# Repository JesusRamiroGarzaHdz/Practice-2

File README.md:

# Practice 2. Developiong the PCB (Layout)

## Objectives

Develop the connection diagrams (layout) from the schematic diagram.

## Introduction

Microcontrollers are all around  he world. Each day, Microcontrollers, are more present in the many aspects of our lives: in our work, inside our houses, and in more. We can find them controlling small devices like cellphones, microwaves, washing machines, and televisions.

A microcontroller is one device or chip that is used to govern one or more processes. For example, the controller that regulates the room temperature of an air conditioner; it has a sensor that continuously measures the internal temperature and, when the preset limits are exceeded, it generates the necessary signals to adjust the temperature.

## State of the Art

### The practices and the PIC microcontroller

The main objective of this practices is to provide students the foundation to fully understand the operation of the PIC18F45K50 microcontroller. This will be achieved through 11 documents that will guide the reader to create their own electronic card or Printed Circuit Board (PCB) and to be able to program it; in order to, execute different functions.

The advantages of ta PIC microcontroller to others on the market, which is why it will be used throughout this manual, are as follows:

- Easy to operate.
- There is enough documentation to work with it and it’s easy to obtain it.
- The price is comparatively lower than its competitors.
- It has a high operating speed.
- Development tools are cheap and easy to use.
- There are a variety of hardware that can record, erase and check the behavior of PIC.
- Once you learn to handle a PIC, it will easier to handle any other models of microcontrollers.

### KiCad EDA Software

KiCad is an open source software suite for Electronic Design Automation (EDA). The programs handle Schematic Capture,
and PCB Layout with Gerber output. The suite runs on Windows, Linux and macOS and is licensed under GNU GPL v3. The
first release date was in 1992 by its original author, Jean-Pierre Charras, but is now currently under development by
the KiCad Developers Team. 

## Results

In this section, you must report the outcomes of the laboratory activities.

### Follow the next 'Project Configuration' Steps

1. In  the  same  project  from  practice  1,  click  on  the  icon ‘Assign PCB footprints to schematic symbols’.  By  doing  so,  you  will  be  able  to  watch  the  footprints associations in a list format. ***NOTE:*** *If a ***‘Confirmation’*** window pops to reassign all the components to a new library format, click ‘No.’*

2. Now it is time to add the corresponding libraries to the Cvpcbprogram.   Download from [here](./modules)  the modules   needed   for   the   project.   Click   on Preferences→Manage Footprint Libraries...and  in this  way  you  will  be  able  to  add  the  modules  from the folder  named  ‘modules.’  Click  on  ‘Project  Specific Libraries...’  tab,  then  click  on  the  button  ‘Browse Libraries...’ and search for the folder  where  you  save the modules. Select all the files and click ‘OK.’Fig.  1 shows the result of the added modules. NOTE:Your KiCad EDA Software must be in english to add the modules.

3. Once  that  is  done,  you  must  associate  the  list  of components  with  its  respective  footprint using Table  I for  guidance.  Be  sure  to  activate  the  option  ‘Filter footprints  list  by  library’ from  the Cvpcbtoolbar. To associate  the  components  showed  in  the middle  column,  double  click  with  their  corresponding footprint from the right column. ***NOTE:*** *Search  all  the  footprints  in  the*  ***‘user’*** *and * 
***‘discrete’*** * added libraries that should be found at the end of the list.*

4. Save   your modifications  by  clicking  **‘Apply,  Save Schematic & Continue,’ and then click ‘OK.’**
5. After that, you may close the Cvpcband go back to the EESchema (Schematic  Editor.)  Save  your  project  by clicking   on File→Save.   Close   the   editor   of   the Schematic and switch back to the **‘Project Manager.’**

6. Once you have the design of the circuit on the schematic, it is time to generate the **‘layout’** of our PCB  using the Netlist  file. On  the Project  Manager program  from KiCad, click on the icon **‘PCB layout editor’** . A new window will appear from the PCBNew. Click **‘Yes’** in the confirmation window.
7. On  the  toolbar  menu  from  the PCBNew click  on  the **‘Page  Settings  for  paper  size  and  texts’**
and modify the size settings to **‘USLetter 8.5x11in.’**

8. After  that,  it  will be  time  to  focus  more  on  design concepts.  You  may  do  so  by  opening  the
menu  of **‘Setup→Design Rules...’**. On   it,   some   final   design characteristics will appear with many millimeter values. Between   them,   you   should   find  the  **‘Clearance’** specification  which  is  the  smallest  spaces  that  it  must exist  between  the tracks  on the  PCB.  You  shall  set the value of this cell to 0.508 mm (0.020 inches.) Next, we set  a  value  of 1.200  mm  (0.047244 inches)on the  cell of **‘Track Width.’** 

9. Switch now to the ‘Global Design Rules’ tab and write, if needed, the minimum values for each an every one of the parameters on the ‘Minimum Allowed Values’ box. Click ‘OK.’

10. Time  to  import  the  Netlist  file.  Go  to  the  toolbar ‘Tools→Update  PCB  from  Schematic...’  and  then click on ‘Update  PCB.’ When  you  close  the  window all the components will appear on the screen.

11.Check in the ‘Layers Manager’ window (located at the right  part  of  your  screen) that all  the needed  boxes  are
checked, as shown:

11.Check in the ‘Layers Manager’ window (located at the right  part  of  your  screen) that all  the needed  boxes  are checke

12. Now you  have  to  define  the  limits  of  the  PCB.  First, highlight  the  ‘Edge.Cuts’  layer.  Then,  select  the  ‘Add  graphic lines’ tool and began to trace the original measures of your copper board (15x20 cm.) You must also define the  cutting  area;  do  not  forget  to  add  a  2.5  cm  margin around the board. To measure the lines, you can use the ‘Add dimension’ tool located on the right.

13. It is your turn to move all the components in the circuit in  order  to  avoid  any  track  intersection  inside  the working   area.   You   can   move   the   components   by positioning your mouse pointer above it and pressing the key [G]. All the components are connected to each other by a group of wires called ratsnest. Make sure that the icon  of  **‘Hide  board  ratsnest’** located  in  the toolbar of the left is highlighted.

14. Now you must link all the connections of you PCB. But before  that,  you  must  change  the  drawing  option  from the right toolbar from ‘Edge.Cuts’ to ‘B.Cu (PgDn)’ (B->Bottom, Cu->Copper.).

15. Start to connect your tracks to each and every one pin on the schematic by using the icon ‘Route Tracks’. Trace  all  the  routes  for  each  net  or  connection  in  your PCB design.

16. Once  your  are  done,  save  your  layout  File->Save  or using the command [Ctrl + S].

17. Your board must look like:

### Report
For this practice, modify only the Conclusion section. Commit an push the changes on the fork of this repository and add
upload the link on Canvas.

### File uploads
Commit and push the files with extensions .pro and .kicad_pcb created once you completed all the steps of the document in the repository.

### Demonstration
Screenshot the image of the complete schematic and upload it at the repository.

## Conclusion

In this second practice we learned how to develop a PCB (layer) for our proyect, this laboratory was by far the hardest one to complete because of the complexity of the software and our lack of experience in this topics. Personally, I had a problem with the libaries that we where asked to use por this practice, in 2 different points during the proccess, the program detected an error in my libraries and marked all my components as "unkonwn" erasing them form my schematic so I had to restart the practice. It was difficult and I had to ask for help to other classmates but at the end I managed to complete the practice and I think I solved it correctly. It was defenitely a bigger challenge than practice 1 but I consider that I have learned a lot about Kicad and how to use it to develop PCBs.

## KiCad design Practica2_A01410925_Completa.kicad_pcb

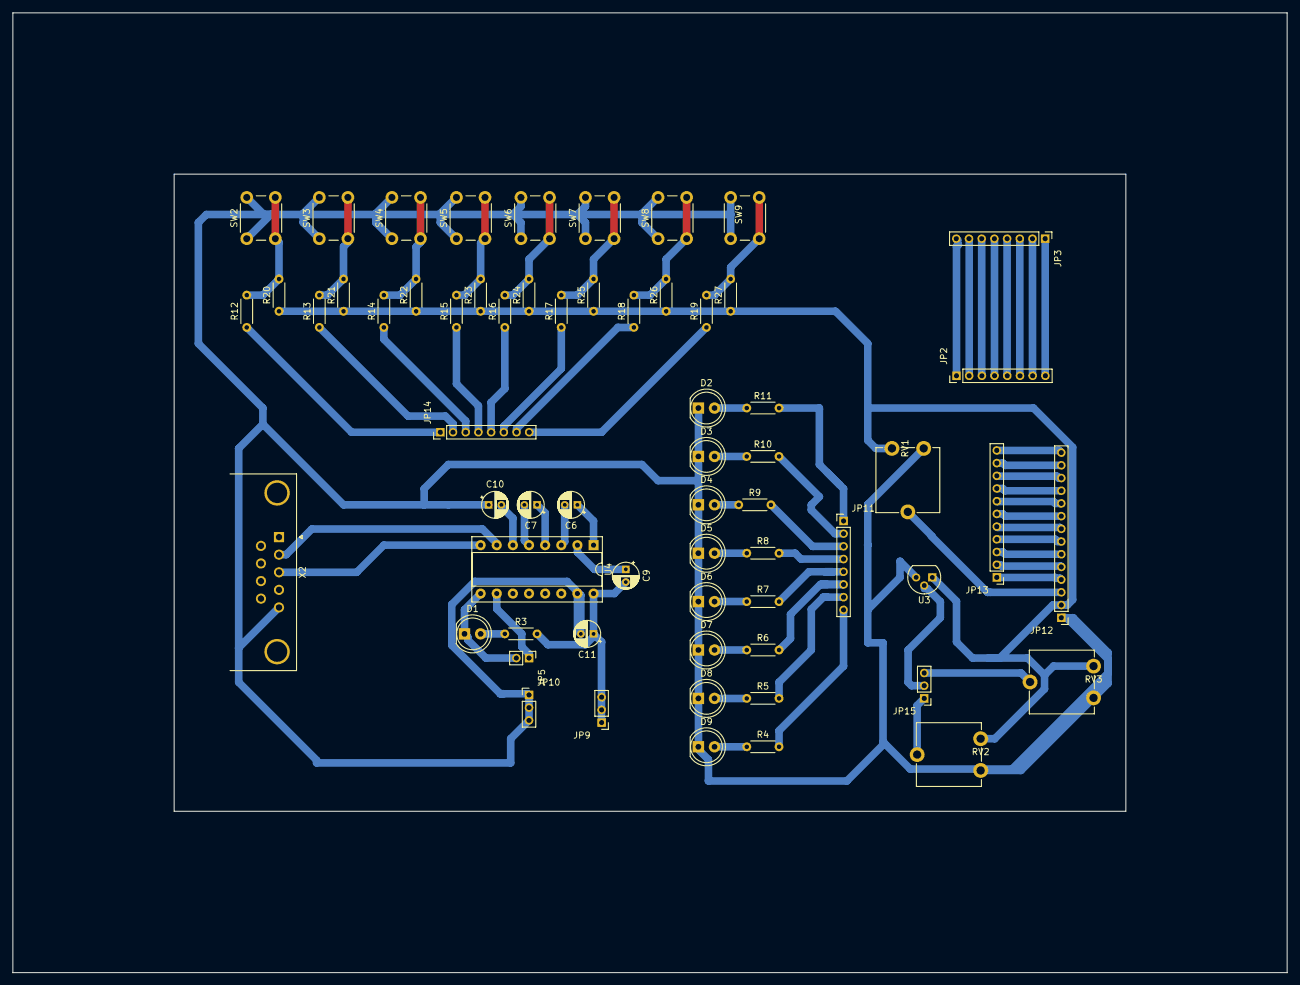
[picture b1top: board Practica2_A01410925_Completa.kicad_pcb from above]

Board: 2 copper layers, 200.7 x 151.1 mm, 63 parts (0 on the bottom side), 68 nets.

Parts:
C6, C7, C9, C10, C11: 10U; CP_Radial_D4.0mm_P2.00mm
D1, D2, D3, D4, D5, D6, D7, D8, D9: LED; LED_D5.0mm
JP2, JP3, JP11, JP14: PINHD-1X8; PinHeader_1x08_P2.00mm_Vertical
JP5: PINHD-1X2; PinHeader_1x02_P2.00mm_Vertical
JP9, JP10, JP15: PINHD-1X3; PinHeader_1x03_P2.00mm_Vertical
JP12: PINHD-1X14; PinHeader_1x14_P2.00mm_Vertical
JP13: PINHD-1X11; PinHeader_1x11_P2.00mm_Vertical
R3, R4, R5, R6, R7, R8, R9, R10, R11: 470; R_Axial_DIN0204_L3.6mm_D1.6mm_P5.08mm_Horizontal
R12, R13, R14, R15, R16, R17, R18, R19: 1K; R_Axial_DIN0204_L3.6mm_D1.6mm_P5.08mm_Horizontal
R20, R21, R22, R23, R24, R25, R26, R27: 4.7K; R_Axial_DIN0204_L3.6mm_D1.6mm_P5.08mm_Horizontal
RV1, RV2, RV3: 10K; Potentiometer_ACP_CA9-V10_Vertical
SW2, SW3, SW4, SW5, SW6, SW7, SW8, SW9: SW_Push; SW_PUSH_6mm
U3: MCP9700A; TO-92
U4: MAX232; DIP-16_W7.62mm_Socket
X2: F09HP; DSUB-9_Male_Horizontal_P2.77x2.84mm_EdgePinOffset4.94mm_Hou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

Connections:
+5VA: C9.2, C11.1, JP9.1, JP9.2, JP9.3, JP12.2, R3.2, R20.1, R21.1, R22.1, R23.1, R24.1, R25.1, R26.1, R27.1, RV1.1, RV2.1, RV3.1, U3.1, U4.16
GNDA: C10.1, C11.2, D2.1, D3.1, D4.1, D5.1, D6.1, D7.1, D8.1, D9.1, JP10.1, JP10.2, JP10.3, JP12.1, RV1.3, RV2.3, RV3.3, SW2.1, SW3.1, SW4.1, SW5.1, SW6.1, SW7.1, SW8.1, SW9.1, U3.3, U4.15, X2.5
unnamed: C6.1, U4.1
unnamed: C6.2, U4.3
unnamed: C7.1, U4.4
unnamed: C7.2, U4.5
unnamed: C9.1, U4.2
unnamed: C10.2, U4.6
unnamed: D1.1, JP5.2, U4.9
unnamed: D1.2, R3.1
unnamed: D2.2, R11.1
unnamed: D3.2, R10.1
unnamed: D4.2, R9.1
unnamed: D5.2, R8.1
unnamed: D6.2, R7.1
unnamed: D7.2, R6.1
unnamed: D8.2, R5.1
unnamed: D9.2, R4.1
unnamed: JP2.1, JP3.8
unnamed: JP2.2, JP3.7
unnamed: JP2.3, JP3.6
unnamed: JP2.4, JP3.5
unnamed: JP2.5, JP3.4
unnamed: JP2.6, JP3.3
unnamed: JP2.7, JP3.2
unnamed: JP2.8, JP3.1
unnamed: JP5.1, U4.10
unnamed: JP11.1, R11.2
unnamed: JP11.2, R10.2
unnamed: JP11.3, R9.2
unnamed: JP11.4, R8.2
unnamed: JP11.5, R7.2
unnamed: JP11.6, R6.2
unnamed: JP11.7, R5.2
unnamed: JP11.8, R4.2
unnamed: JP12.3, RV1.2
unnamed: JP12.4, JP13.1
unnamed: JP12.5, JP13.2
unnamed: JP12.6, JP13.3
unnamed: JP12.7, JP13.4
unnamed: JP12.8, JP13.5
unnamed: JP12.9, JP13.6
unnamed: JP12.10, JP13.7
unnamed: JP12.11, JP13.8
unnamed: JP12.12, JP13.9
unnamed: JP12.13, JP13.10
unnamed: JP12.14, JP13.11
unnamed: JP14.1, R12.1
unnamed: JP14.2, R13.1
unnamed: JP14.3, R14.1
unnamed: JP14.4, R15.1
unnamed: JP14.5, R16.1
unnamed: JP14.6, R17.1
unnamed: JP14.7, R18.1
unnamed: JP14.8, R19.1
unnamed: JP15.1, RV2.2
unnamed: JP15.2, U3.2
unnamed: JP15.3, RV3.2
unnamed: R12.2, R20.2, SW2.2
unnamed: R13.2, R21.2, SW3.2
unnamed: R14.2, R22.2, SW4.2
unnamed: R15.2, R23.2, SW5.2
unnamed: R16.2, R24.2, SW6.2
unnamed: R17.2, R25.2, SW7.2
unnamed: R18.2, R26.2, SW8.2
unnamed: R19.2, R27.2, SW9.2
unnamed: U4.7, X2.2
unnamed: U4.8, X2.3

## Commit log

2020-09-22 Update README.md
    Conclusion modified
